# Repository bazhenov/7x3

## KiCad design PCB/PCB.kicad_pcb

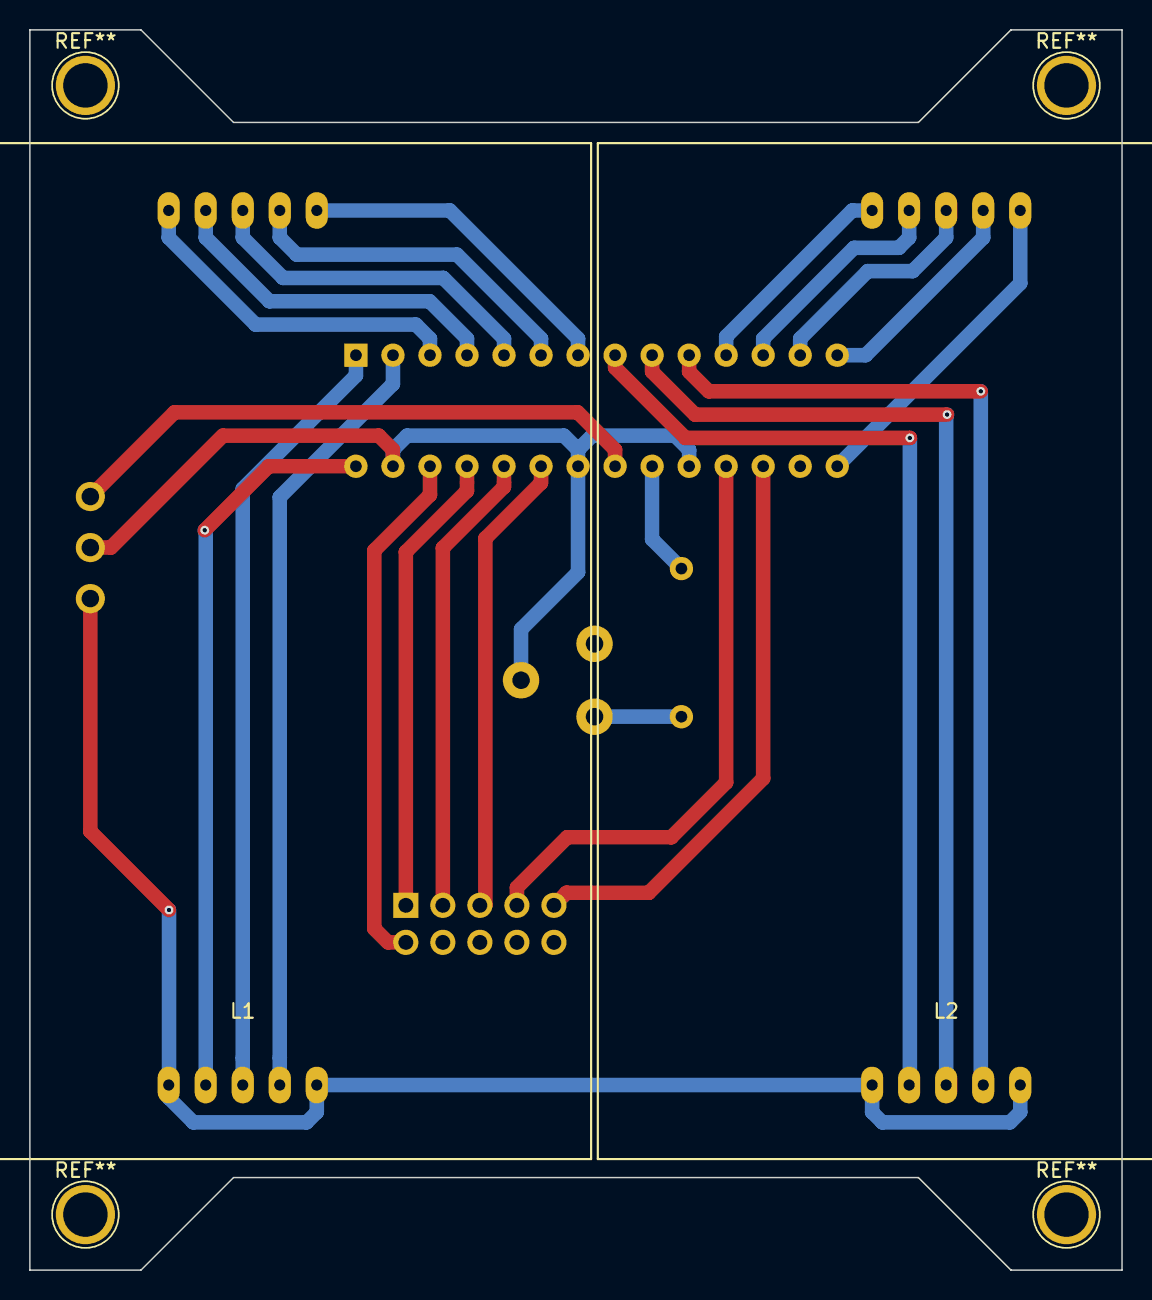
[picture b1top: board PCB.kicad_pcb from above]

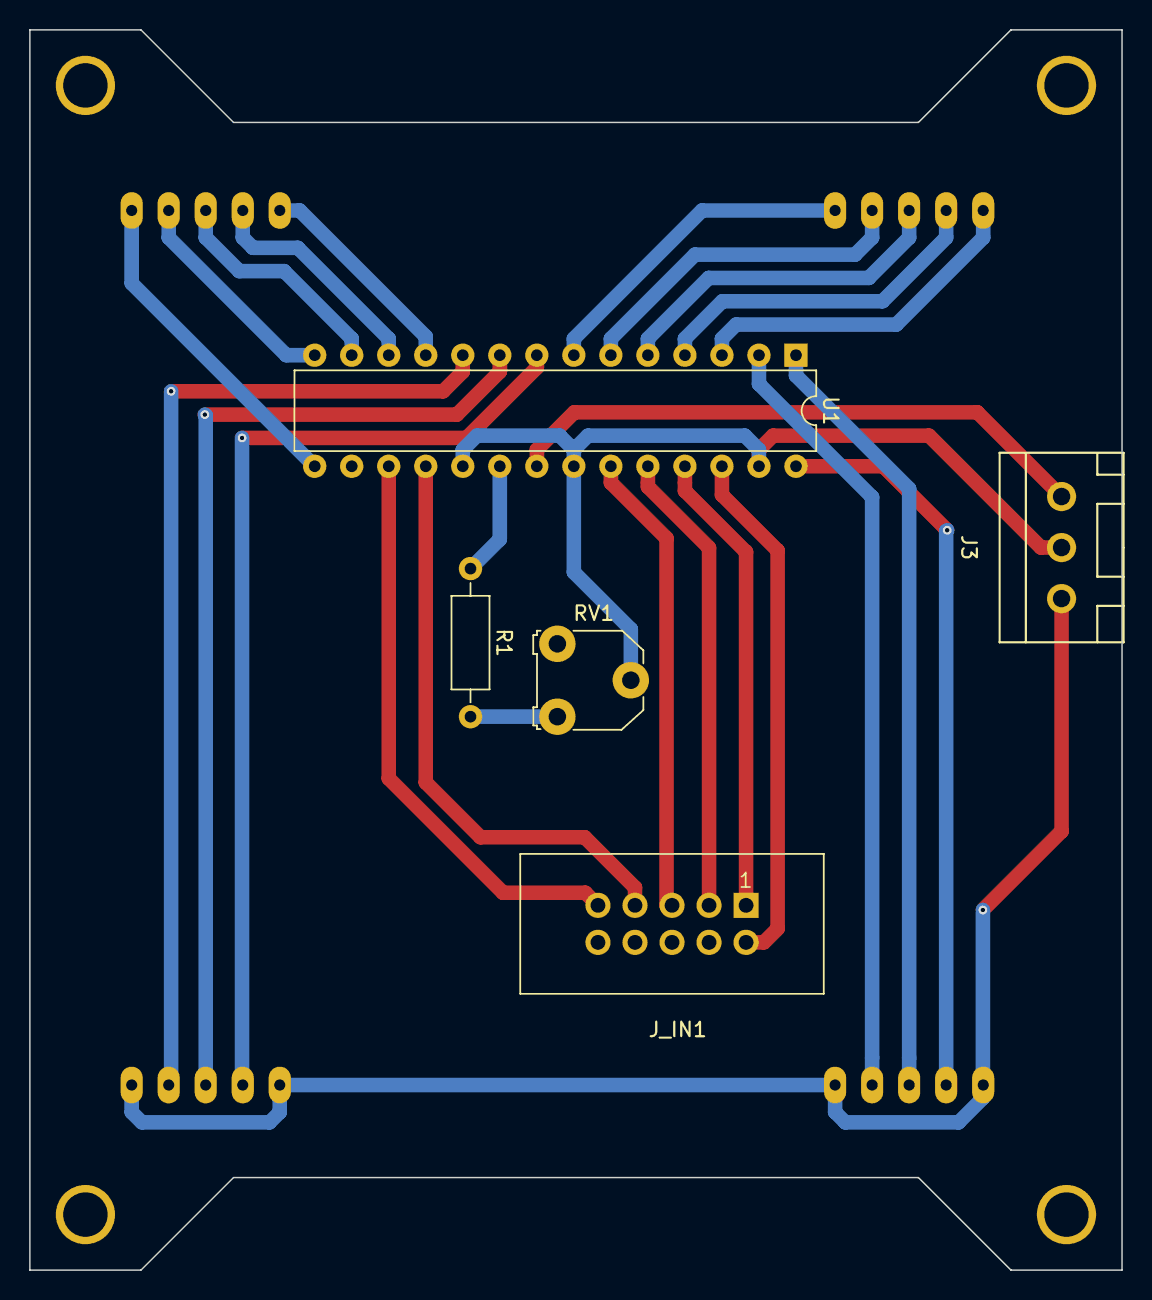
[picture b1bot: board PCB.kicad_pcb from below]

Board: 2 copper layers, 74.9 x 85.1 mm, 7 parts (5 on the bottom side), 27 nets.

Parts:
J3: CONN_PWR; WAGO_734_3pin_Straight
J_IN1: CONN_IF; IDC_Header_Straight_10pins
L1, L2: KYX-23101BS
R1: 1k; R_Axial_DIN0207_L6.3mm_D2.5mm_P10.16mm_Horizontal
RV1: 2K; Potentiometer_Triwood_RM-065
U1: TLC5940NT; DIP-28_W7.62mm

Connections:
/led-module/1DP: L1.8, U1.5
/led-module/1SEG_A: L1.7, U1.6
/led-module/1SEG_B: L1.6, U1.7
/led-module/1SEG_C: L1.4, U1.2
/led-module/1SEG_D: L1.3, U1.1
/led-module/1SEG_E: L1.2, U1.28
/led-module/1SEG_F: L1.9, U1.4
/led-module/1SEG_G: L1.10, U1.3
/led-module/2DP: L2.8, U1.13
/led-module/2SEG_A: L2.7, U1.14
/led-module/2SEG_B: L2.6, U1.15
/led-module/2SEG_C: L2.4, U1.10
/led-module/2SEG_D: L2.3, U1.9
/led-module/2SEG_E: L2.2, U1.8
/led-module/2SEG_F: L2.9, U1.12
/led-module/2SEG_G: L2.10, U1.11
/led-module/BLANK: J_IN1.5, U1.23
/led-module/GSCLK: J_IN1.7, U1.18
/led-module/SCLK: J_IN1.1, U1.25
/led-module/SIN: J_IN1.2, U1.26
/led-module/SOUT: J_IN1.9, U1.17
/led-module/VCC: J3.3, U1.21
/led-module/VLED: J3.1, L1.1, L1.5, L2.1, L2.5
/led-module/XLAT: J_IN1.3, U1.24
Earth: J3.2, RV1.2, U1.19, U1.22, U1.27
unnamed: R1.1, U1.20
unnamed: R1.2, RV1.3

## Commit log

2017-04-01 Some schematic changes
2017-04-11 Network integration
2017-05-05 Перегруппировка коннекторов модуля
2017-05-18 tracing
2017-05-18 layoyt changed
2017-05-18 layput complete
2017-05-18 Layout done
2017-09-08 Some changes in PCB
2017-10-09 KiCad 4.0.7 update
